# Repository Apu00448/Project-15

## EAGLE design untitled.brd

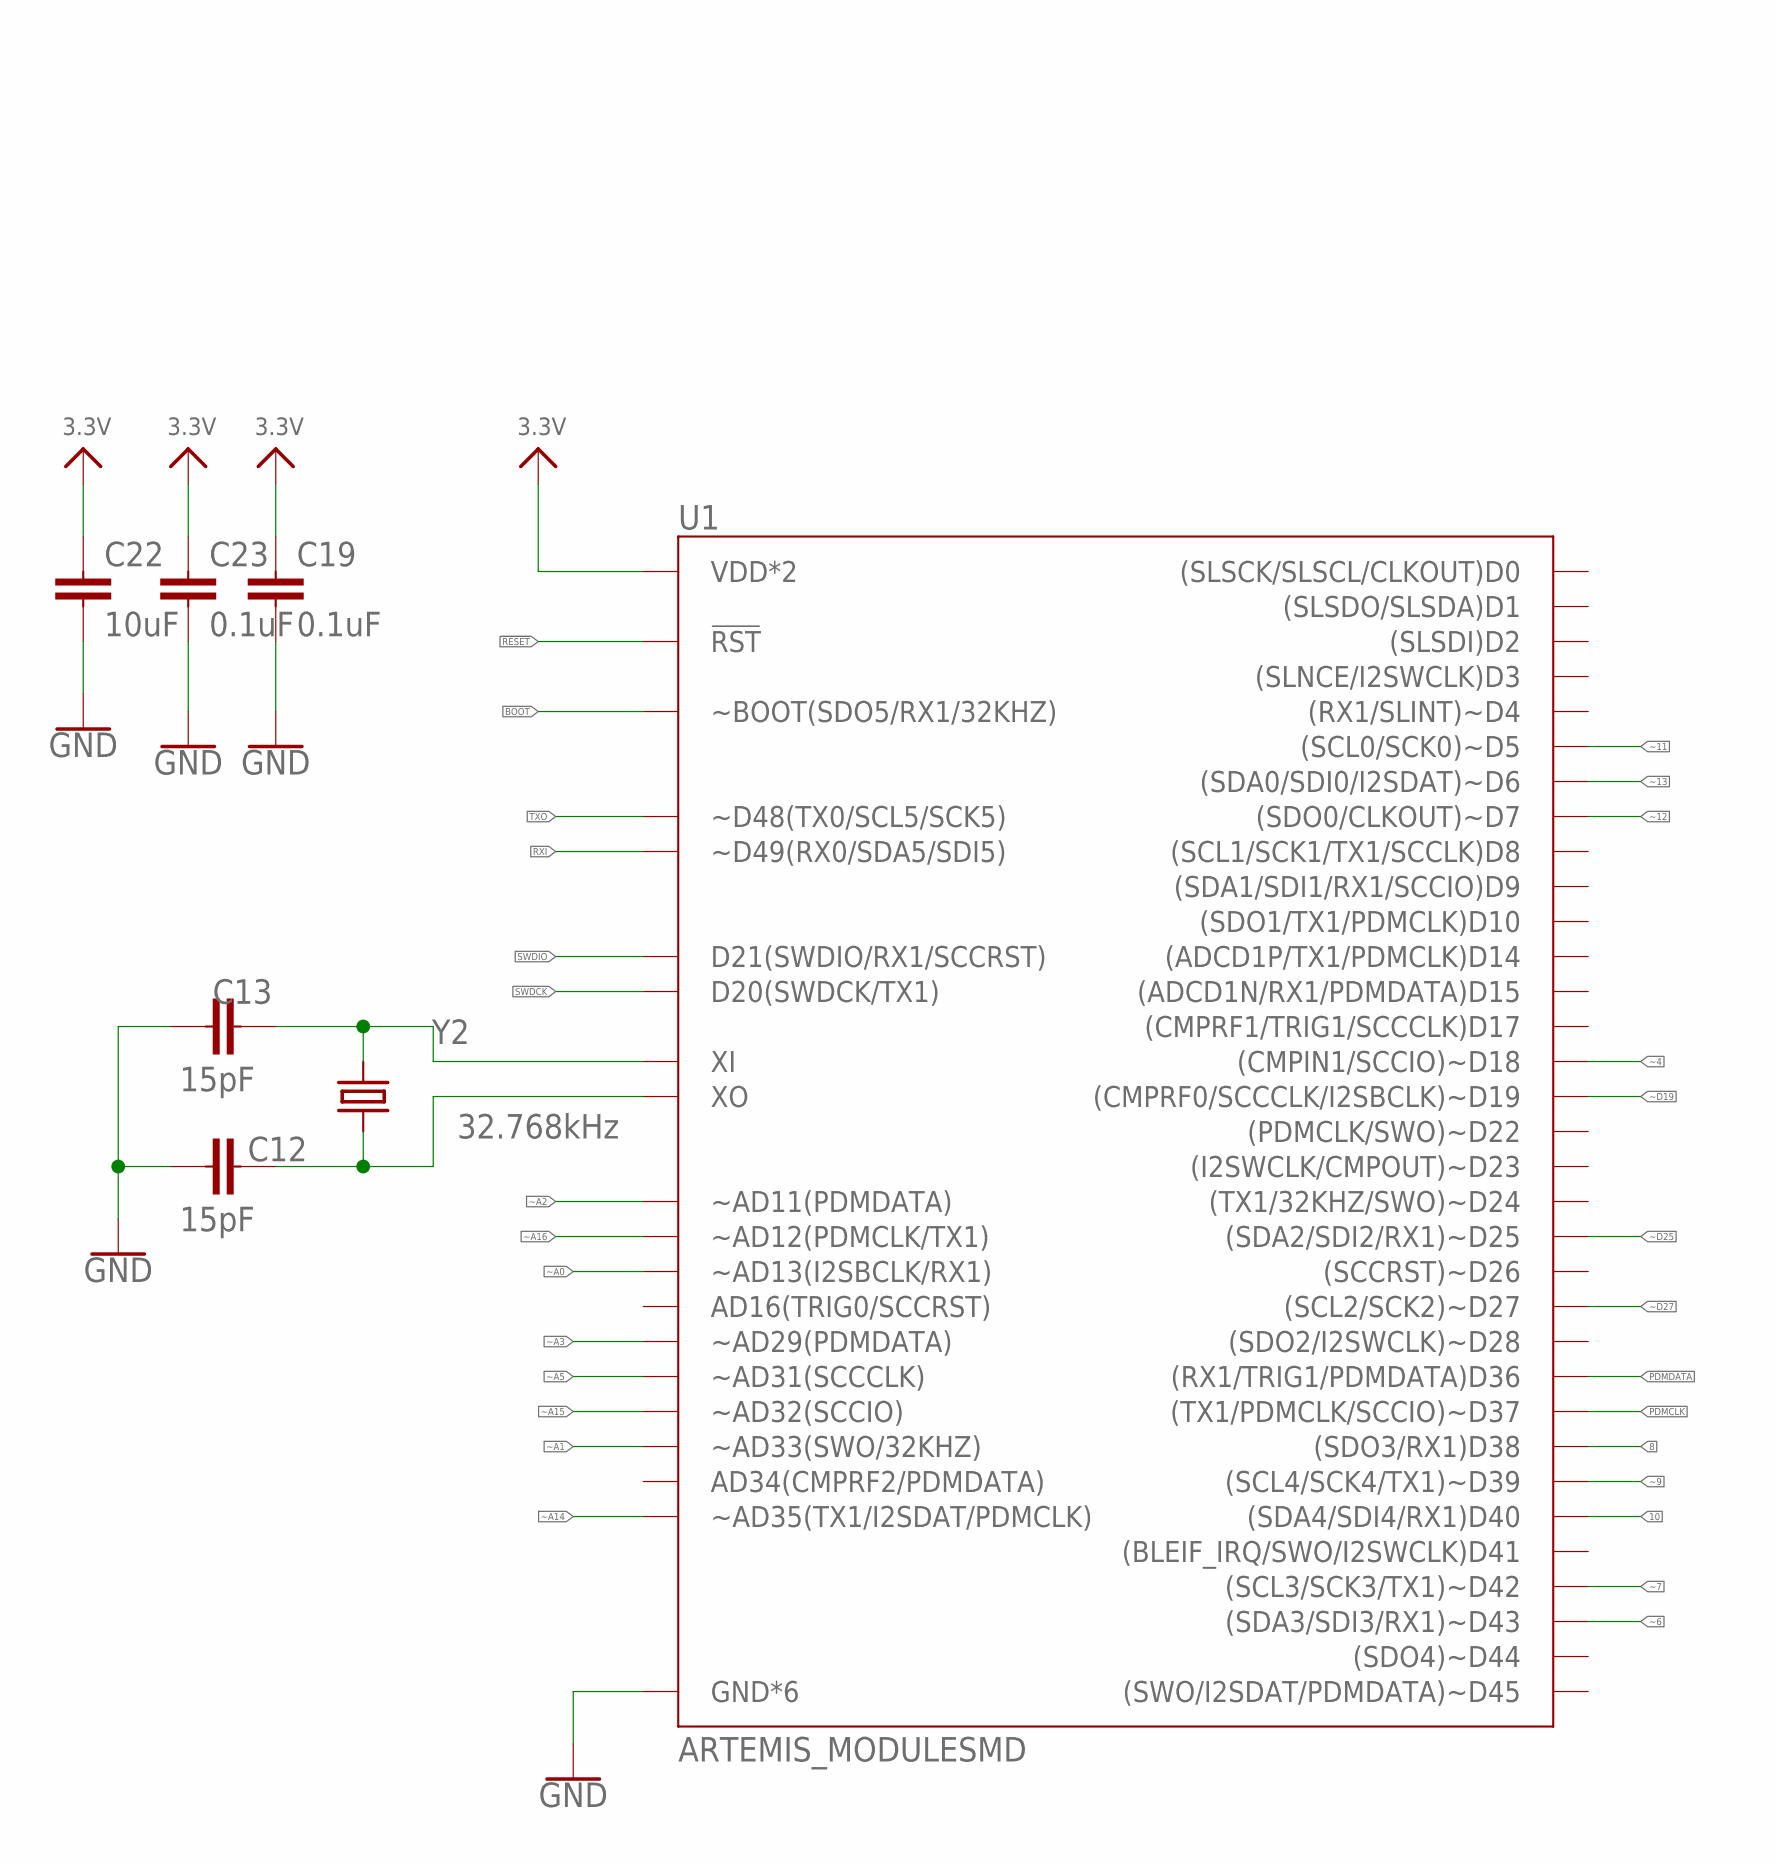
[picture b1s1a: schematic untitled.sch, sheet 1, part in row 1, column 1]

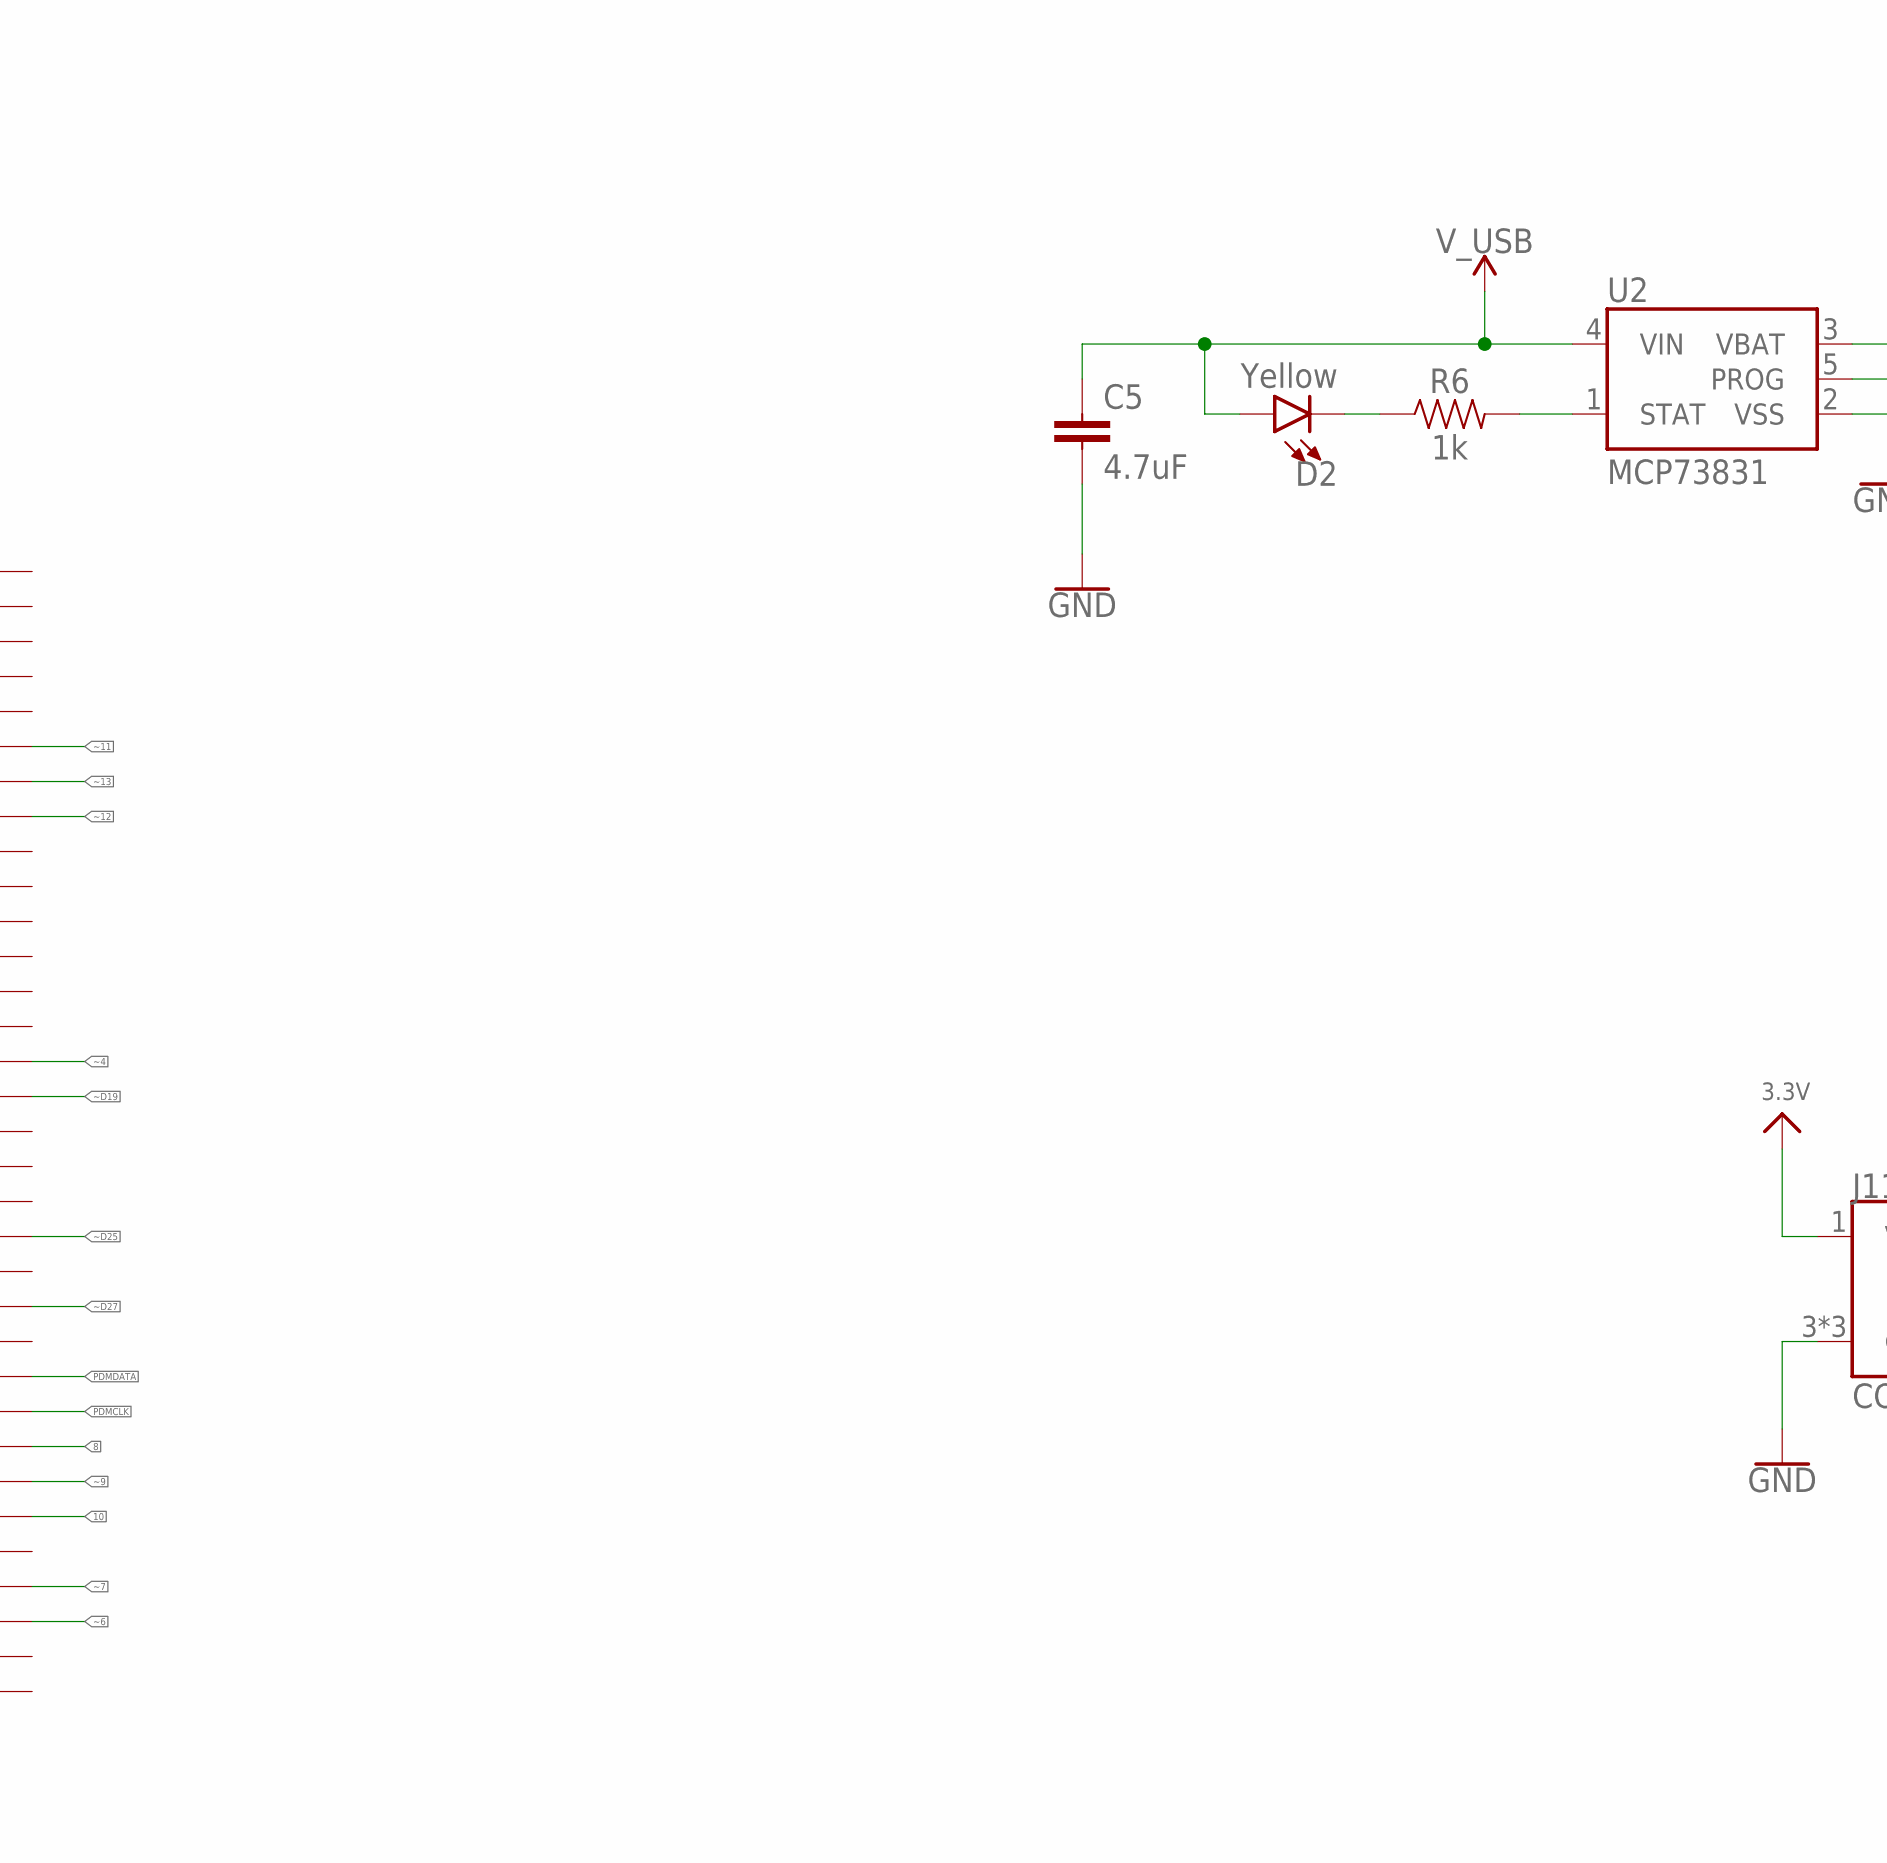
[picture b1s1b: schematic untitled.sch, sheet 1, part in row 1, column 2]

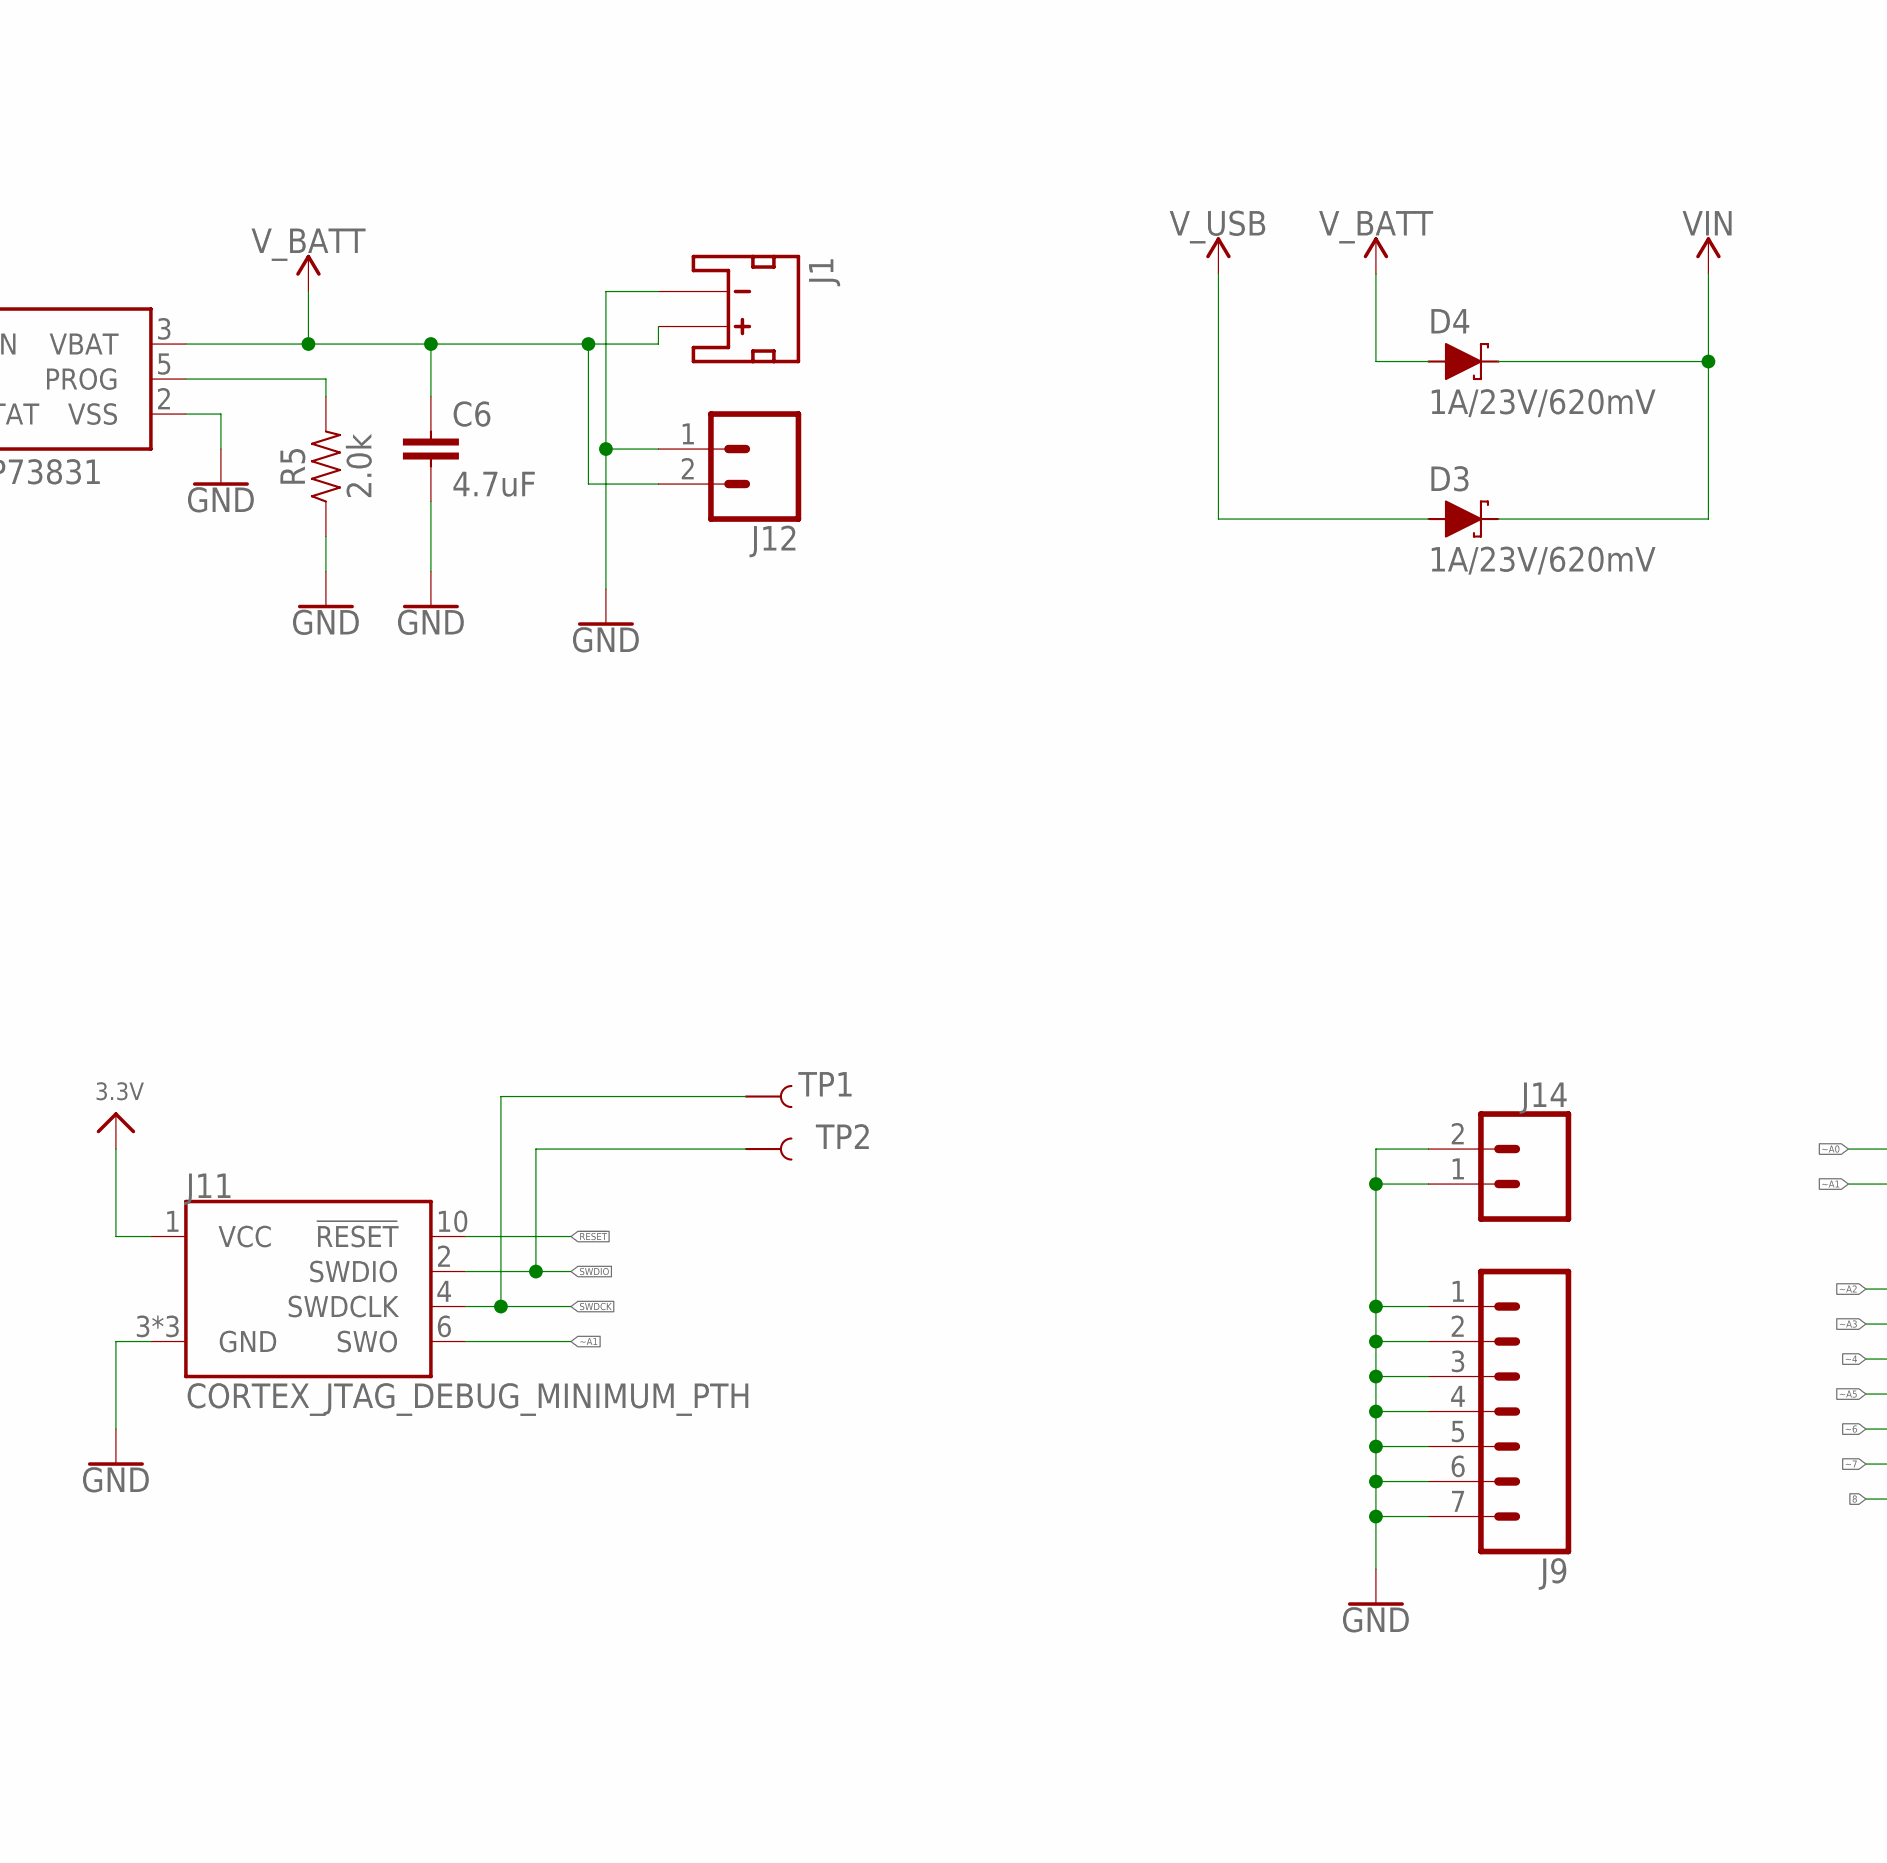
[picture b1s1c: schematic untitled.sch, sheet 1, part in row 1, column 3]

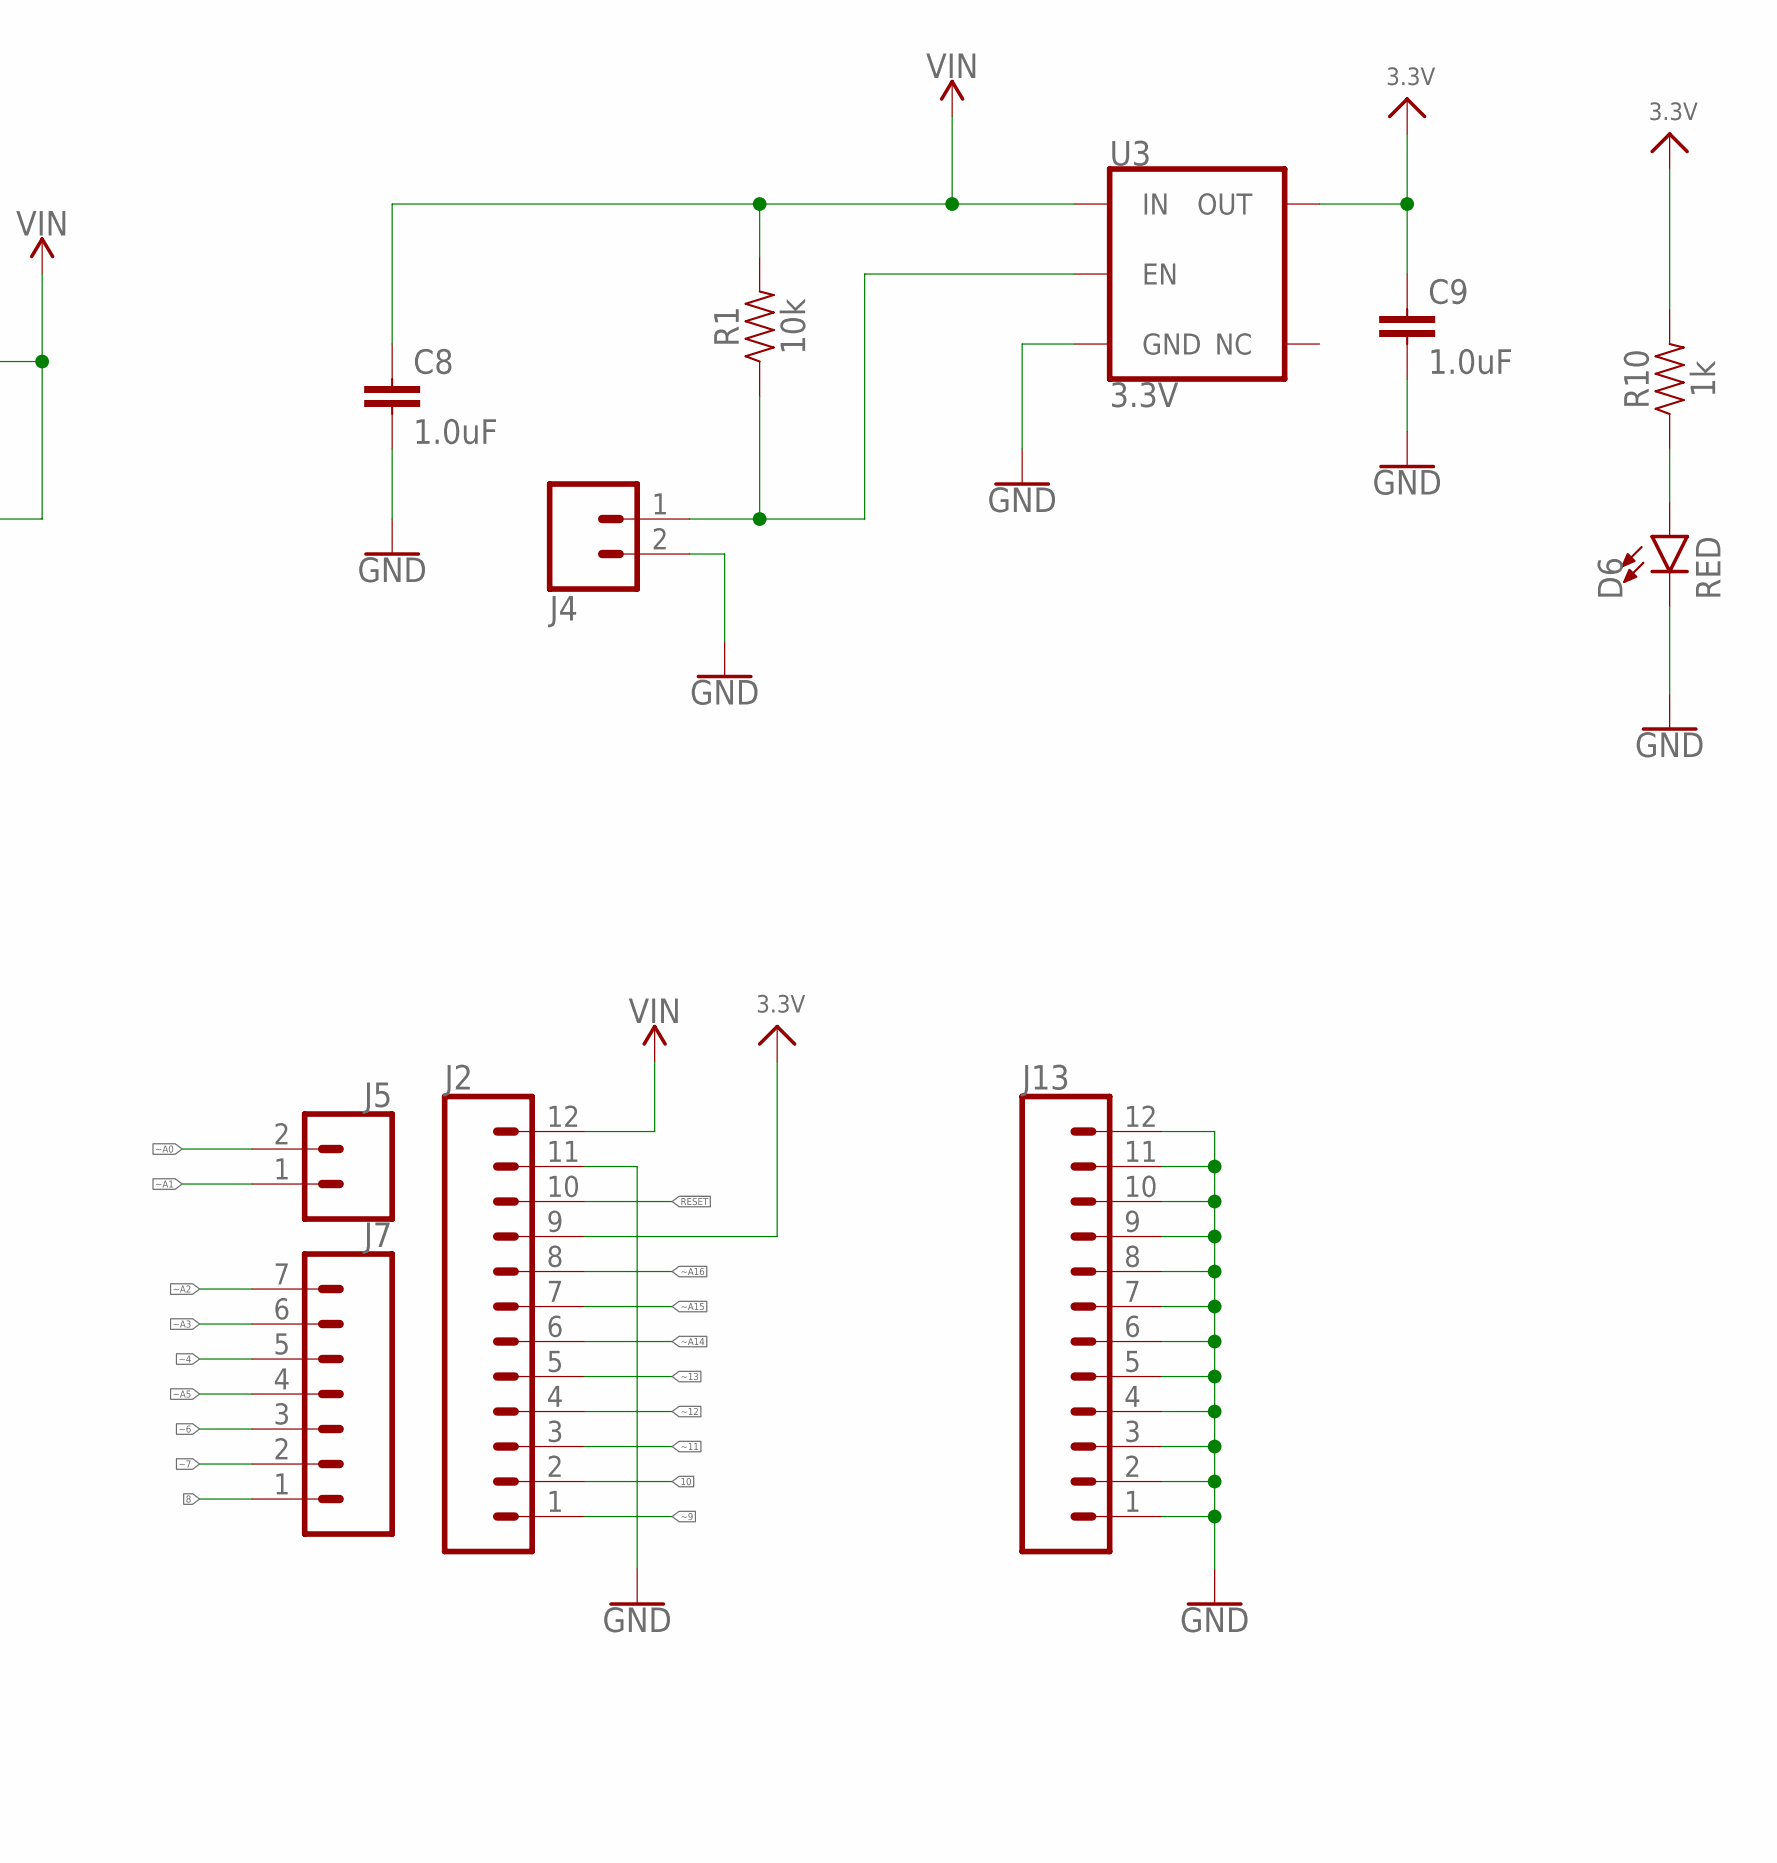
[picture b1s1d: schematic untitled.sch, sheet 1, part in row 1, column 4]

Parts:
C5, C6: 4.7uF; 0603
C8, C9: 1.0uF; 0402-TIGHT
C12, C13: 15pF; 0603
C19, C23: 0.1uF; 0402-TIGHT
C22: 10uF; 0603
D2: Yellow; LED-0603
D3, D4: 1A/23V/620mV; SOD-323
D6: RED; LED-0603
J1: JST_2MM_MALE; JST-2-SMD
J2, J13: CONN_12NO_SILK; 1X12_NO_SILK
J4, J5, J12, J14: CONN_021X02_NO_SILK; 1X02_NO_SILK
J7, J9: CONN_07NO_SILK; 1X07_NO_SILK
J11: CORTEX_JTAG_DEBUG_MINIMUM_PTH; 2X5-PTH-1.27MM
R1: 10k; 0603
R5: 2.0k; 0603
R6, R10: 1k; 0603
TP1, TP2: TEST-POINT3X5; PAD.03X.05
U1: ARTEMIS_MODULESMD; ARTEMIS_FP
U2: MCP73831; SOT23-5
U3: 3.3V; SOT23-5
Y2: 32.768kHz; CRYSTAL-SMD-3.2X1.5MM

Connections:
3.3V: C9.1, C19.1, C22.1, C23.1, J2.9, J11.1 (VCC), R10.2, U1.VDD@36 (VDD*2), U1.VDD@37 (VDD*2), U3.5 (OUT); also elsewhere on the board
8: J7.1, U1.D38 ((SDO3/RX1)D38)
10: J2.2, U1.D40 ((SDA4/SDI4/RX1)D40)
!RESET: J2.10, J11.10 (!RESET), U1.~RST (!RST); also elsewhere on the board
BOOT: U1.BOOT (~BOOT(SDO5/RX1/32KHZ)); also elsewhere on the board
GND: C5.2, C6.2, C8.2, C9.2, C12.1, C13.1, C19.2, C22.2, C23.2, D6.C, J1.1 (-), J2.11, J4.2, J9.1, J9.2, J9.3, J9.4, J9.5, J9.6, J9.7, J11.3 (GND), J11.5 (GND), J11.9 (GND), J12.1, J13.1, J13.2, J13.3, J13.4, J13.5, J13.6, J13.7, J13.8, J13.9, J13.10, J13.11, J13.12, J14.1, J14.2, R5.1, U1.GND@1 (GND*6), U1.GND@22 (GND*6), U1.GND@38 (GND*6), U1.GND@39 (GND*6), U1.GND@47 (GND*6), U1.GND@59 (GND*6), U2.2 (VSS), U3.2 (GND); also elsewhere on the board
unnamed: D6.A, R10.1
unnamed: D2.C, R6.1
unnamed: R6.2, U2.1 (STAT)
unnamed: R5.2, U2.5 (PROG)
unnamed: J4.1, R1.1, U3.3 (EN)
unnamed: C13.2, U1.XI, Y2.P$2 (2)
unnamed: C12.2, U1.XO, Y2.P$1 (1)
PDMCLK: U1.~D37 ((TX1/PDMCLK/SCCIO)~D37); also elsewhere on the board
PDMDATA: U1.D36 ((RX1/TRIG1/PDMDATA)D36); also elsewhere on the board
RXI: U1.RXI-0 (~D49(RX0/SDA5/SDI5))
SWDCK: J11.4 (SWDCLK), TP1.1, U1.SWDCK (D20(SWDCK/TX1))
SWDIO: J11.2 (SWDIO), TP2.1, U1.SWDIO (D21(SWDIO/RX1/SCCRST))
TXO: U1.TXO-0 (~D48(TX0/SCL5/SCK5))
VIN: C8.1, D3.C, D4.C, J2.12, R1.2, U3.1 (IN)
V_BATT: C6.1, D4.A, J1.2 (+), J12.2, U2.3 (VBAT)
V_USB: C5.1, D2.A, D3.A, U2.4 (VIN); also elsewhere on the board
~4: J7.5, U1.~D18 ((CMPIN1/SCCIO)~D18)
~6: J7.3, U1.~D43 ((SDA3/SDI3/RX1)~D43)
~7: J7.2, U1.~D42 ((SCL3/SCK3/TX1)~D42)
~9: J2.1, U1.~D39 ((SCL4/SCK4/TX1)~D39)
~11: J2.3, U1.~D5 ((SCL0/SCK0)~D5)
~12: J2.4, U1.D7 ((SDO0/CLKOUT)~D7)
~13: J2.5, U1.~D6 ((SDA0/SDI0/I2SDAT)~D6)
~A0: J5.2, U1.~AD13 (~AD13(I2SBCLK/RX1))
~A1: J5.1, J11.6 (SWO), U1.~AD33/SWO (~AD33(SWO/32KHZ))
~A2: J7.7, U1.~AD11 (~AD11(PDMDATA))
~A3: J7.6, U1.~AD29 (~AD29(PDMDATA))
~A5: J7.4, U1.~AD31 (~AD31(SCCCLK))
~A14: J2.6, U1.~AD35 (~AD35(TX1/I2SDAT/PDMCLK))
~A15: J2.7, U1.~AD32 (~AD32(SCCIO))
~A16: J2.8, U1.~AD12 (~AD12(PDMCLK/TX1))
~D19: U1.~D19 ((CMPRF0/SCCCLK/I2SBCLK)~D19); also elsewhere on the board
~D25: U1.~D25 ((SDA2/SDI2/RX1)~D25); also elsewhere on the board
~D27: U1.~D27 ((SCL2/SCK2)~D27); also elsewhere on the board

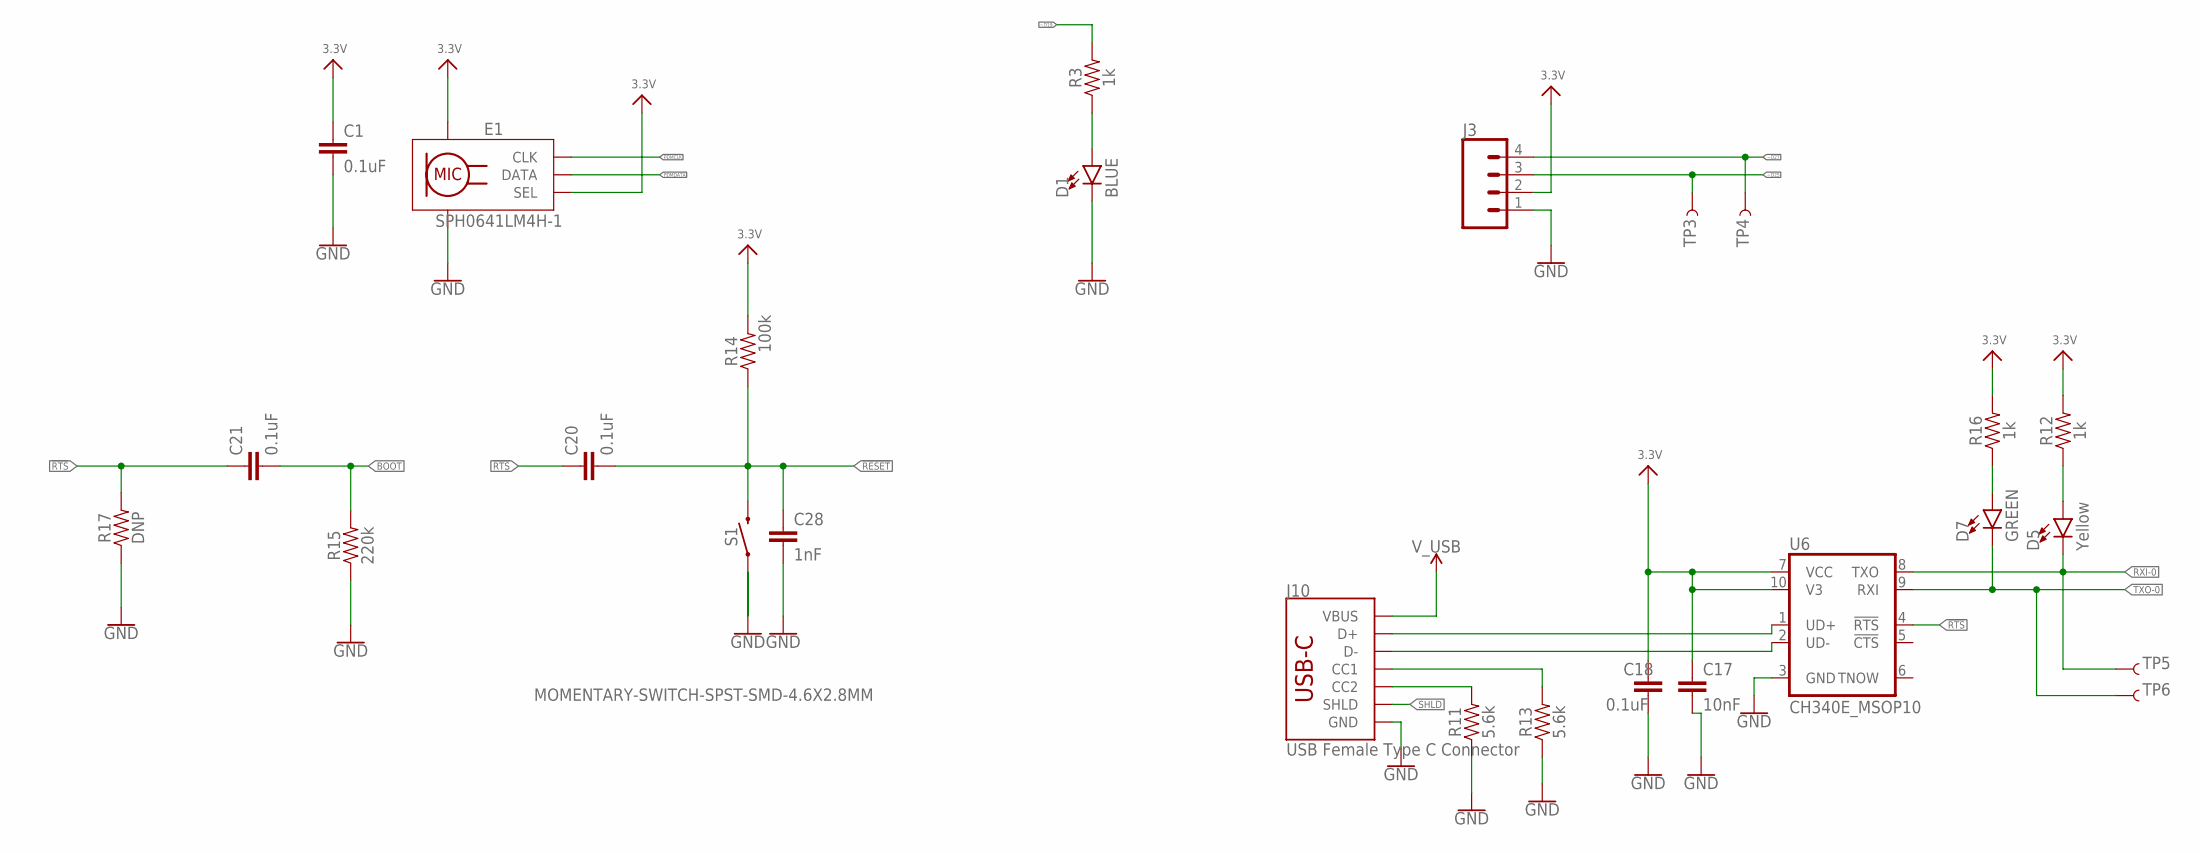
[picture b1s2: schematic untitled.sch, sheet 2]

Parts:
C1: 0.1uF; 0402-TIGHT
C17: 10nF; 0603
C18, C20, C21: 0.1uF; 0603
C28: 1nF; 0603
D1: BLUE; LED-0603
D5: Yellow; LED-0603
D7: GREEN; LED-0603
E1: SPH0641LM4H-1; SPH0641LM4H-1_MICROPHONE
J3: CONN_04SMD2; JST04_1MM_RA
J10: USB Female Type C Connector; USB-C-16P-4LAYER-ISOLATED
R3, R12, R16: 1k; 0603
R11, R13: 5.6k; 0603
R14: 100k; 0603
R15: 220k; 0603
R17: DNP; 0603
S1: MOMENTARY-SWITCH-SPST-SMD-4.6X2.8MM; TACTILE_SWITCH_SMD_4.6X2.8MM
TP3, TP4, TP5, TP6: TEST-POINT3X5; PAD.03X.05
U6: CH340E_MSOP10; MSOP10

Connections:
3.3V: C1.1, C17.1, C18.1, E1.2 (SEL), E1.5 (VDD), J3.2, R12.2, R14.2, R16.2, U6.7 (VCC), U6.10 (V3); also elsewhere on the board
!RESET: C20.2, C28.1, R14.1, S1.3 (2), S1.4 (2); also elsewhere on the board
!RTS: C20.1, C21.1, R17.2, U6.4 (!RTS)
BOOT: C21.2, R15.2; also elsewhere on the board
GND: C1.2, C17.2, C18.2, C28.2, D1.C, E1.3 (GND), E1.6 (GND), E1.7 (GND), E1.8 (GND), J3.1, J10.GND, J10.GND2 (GND), R11.1, R13.1, R15.1, R17.1, S1.1, S1.2 (1), U6.3 (GND); also elsewhere on the board
unnamed: J10.A6 (D+), J10.B6 (D+), U6.1 (UD+)
unnamed: D1.A, R3.1
unnamed: J10.A7 (D-), J10.B7 (D-), U6.2 (UD-)
unnamed: J10.B5 (CC2), R11.2
unnamed: J10.A5 (CC1), R13.2
unnamed: D7.A, R16.1
unnamed: D5.A, R12.1
PDMCLK: E1.4 (CLK); also elsewhere on the board
PDMDATA: E1.1 (DATA); also elsewhere on the board
RXI-0: D5.C, TP5.1, U6.8 (TXO)
SHLD: J10.SHLD1 (SHLD), J10.SHLD2 (SHLD), J10.SHLD3 (SHLD), J10.SHLD4 (SHLD), J10.SHLD5 (SHLD), J10.SHLD6 (SHLD), J10.SHLD7 (SHLD), J10.SHLD8 (SHLD)
TXO-0: D7.C, TP6.1, U6.9 (RXI)
V_USB: J10.VBUS1 (VBUS), J10.VBUS2 (VBUS); also elsewhere on the board
~D19: R3.2; also elsewhere on the board
~D25: J3.3, TP3.1; also elsewhere on the board
~D27: J3.4, TP4.1; also elsewhere on the board

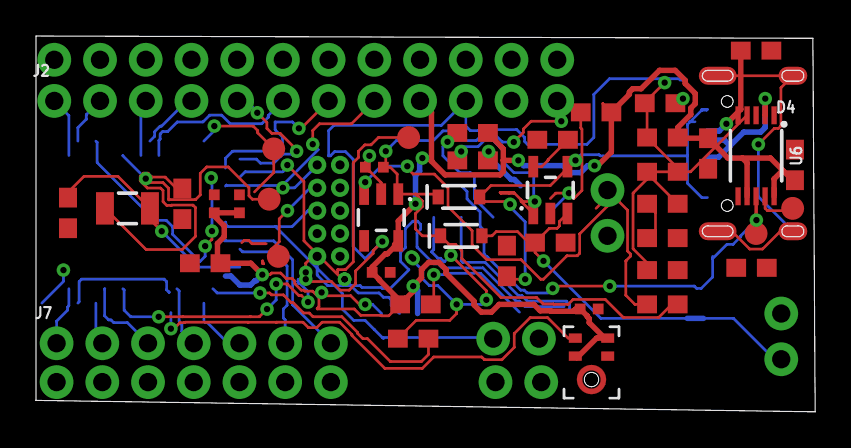
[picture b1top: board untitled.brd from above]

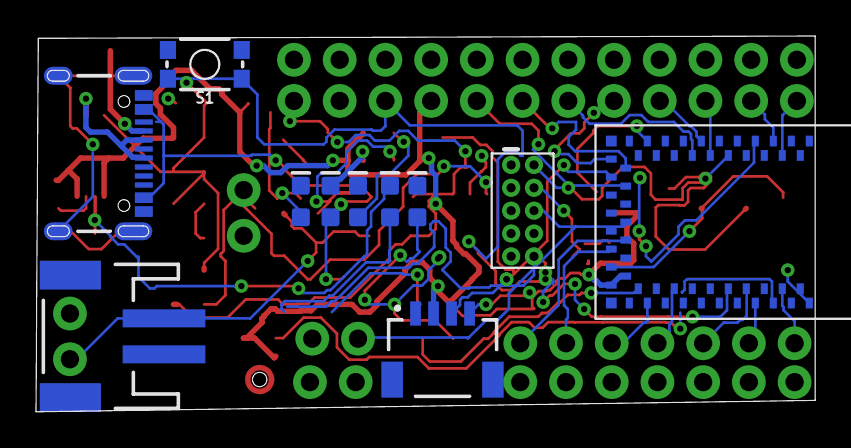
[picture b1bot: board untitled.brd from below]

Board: 2 copper layers, 43.3 x 20.9 mm, 59 parts (11 on the bottom side), 49 nets.

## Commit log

2024-01-03 Red Board -Eagle

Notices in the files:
parts and their libraries:
SparkFun-Capacitors: Licensing: Creative Commons ShareAlike 4.0 International - https://creativecommons.org/licenses/by-sa/4.0
microbuilder: This work is placed in the public domain, and may be freely used for commercial and non-commercial work with the following conditions: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
